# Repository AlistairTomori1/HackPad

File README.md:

# My HackPad

My HackPad is a 6-key (2x3) macropad built around the Seeed XIAO RP2040. It includes 2 EC11 rotary encoders (one for volume, one for timeline scrubbing) and a 0.91 inch 128x32 I2C OLED display (SSD1306) for status and layer info.

## Features
- 6x MX-style keys (2 columns x 3 rows matrix)
- 2x EC11 rotary encoder 1 for Volume, the other is for moving through video timeline
- 0.91 inch 128x32 I2C OLED (pin order: GND-VCC-SCL-SDA)
- KMK (CircuitPython) firmware with layers
- 3D-printed case designed to fit the PCB, OLED, and encoder cleanly

## Photos

## Schematic

Notes:
- Keys are wired as a 2x3 matrix with 1N4148 diodes to prevent ghosting.
- OLED uses I2C (SDA/SCL) and is powered from VBUS (5V).
- There are two encoders; each uses two GPIO pins plus a shared GND common (4 GPIO total).

## PCB

Notes:
- Switches are laid out on standard MX spacing.
- Diodes are placed close to their switches for clean routing.
- XIAO is positioned so the USB port is accessible at the board edge.
- Silkscreen includes the project name plus a "XIAO HERE" orientation label.

## Case and CAD

How it fits together:
- Top plate holds switches and keycaps.
- Middle cavity supports the PCB and provides clearance for solder joints.
- OLED sits above the key cluster.
- Encoder is mounted at the top-right with knob clearance.
- Bottom closes the case and provides mounting points.

(Designed for 3D printing.)

## Firmware Overview (KMK / CircuitPython)
This project uses KMK firmware (Python) for fast iteration.

Default behavior:
- Layer 0:
  - Keys: common editing macros (copy/paste/undo/redo, etc.)
  - Encoder 1: volume up/down
  - Encoder 2: timeline scrub (left/right)
- Layer 1:
  - Keys: media controls
  - Encoder 1: previous/next track
  - Encoder 2: fine scrub (Shift + left/right)

Firmware file:
- `firmware/main.py`

## BOM (Bill of Materials)
Everything needed to build this hackpad:

Electronics:
- 1x Seeed XIAO RP2040
- 6x MX-style switches
- 6x 1N4148 diodes (DO-35, through-hole)
- 2x EC11 rotary encoders
- 1x 0.91 inch 128x32 I2C OLED display (SSD1306, pin order: GND-VCC-SCL-SDA)
- 1x 1x4 2.54mm pin header (for the OLED)
- 1x PCB board

Hardware and Case:
- 6x Blank DSA keycaps (White)
- 3D-printed case (top and bottom, or top/middle/bottom depending on your design)
- 4x M3x16mm screws
- 4x M3 heatset inserts (5x4mm)

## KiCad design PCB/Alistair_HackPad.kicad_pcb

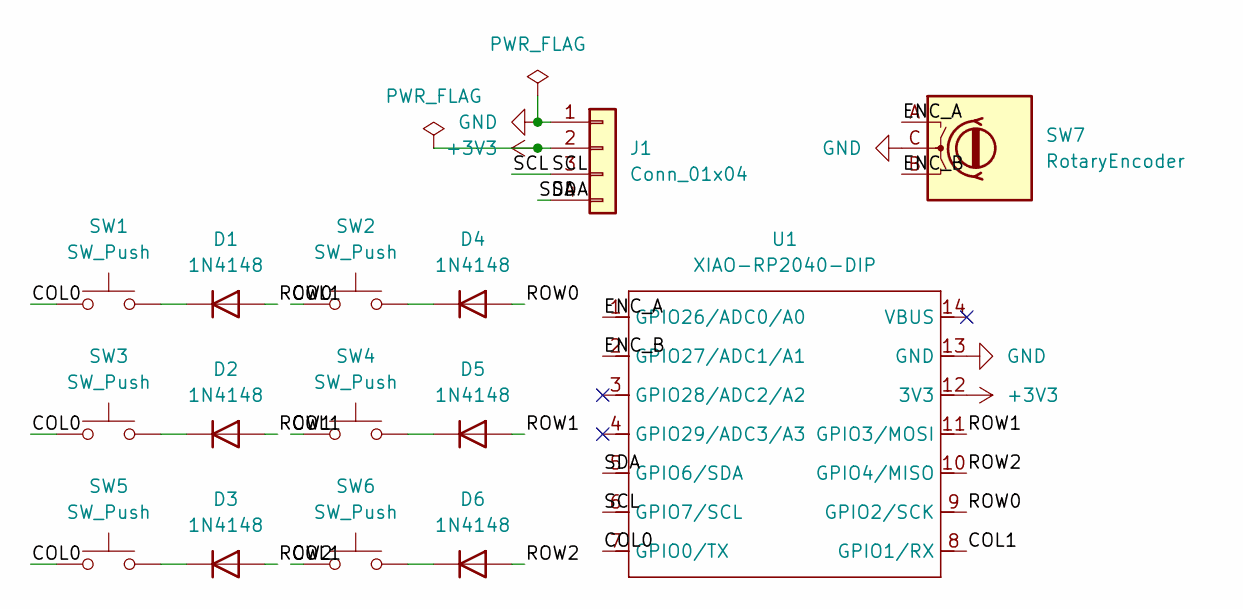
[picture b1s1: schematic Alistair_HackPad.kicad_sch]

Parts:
D1, D2, D3, D4, D5, D6: 1N4148; D_DO-35_SOD27_P7.62mm_Horizontal
J1: Conn_01x04; PinHeader_1x04_P2.54mm_Vertical
SW1, SW2, SW3, SW4, SW5, SW6: SW_Push; SW_Cherry_MX_1.00u_PCB
SW7: RotaryEncoder; RotaryEncoder_Alps_EC11E-Switch_Vertical_H20mm
U1: XIAO-RP2040-DIP

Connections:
+3V3: J1.2, U1.12 (3V3)
/COL0: SW1.1, SW3.1, SW5.1, U1.7 (GPIO0/TX)
/COL1: SW2.1, SW4.1, SW6.1, U1.8 (GPIO1/RX)
/ENC_A: SW7.A, U1.1 (GPIO26/ADC0/A0)
/ENC_B: SW7.B, U1.2 (GPIO27/ADC1/A1)
/ROW0: D1.2 (A), D4.2 (A), U1.9 (GPIO2/SCK)
/ROW1: D2.2 (A), D5.2 (A), U1.11 (GPIO3/MOSI)
/ROW2: D3.2 (A), D6.2 (A), U1.10 (GPIO4/MISO)
/SCL: J1.3, U1.6 (GPIO7/SCL)
/SDA: J1.4, U1.5 (GPIO6/SDA)
GND: J1.1, SW7.C, U1.13 (GND)
unnamed: D1.1 (K), SW1.2
unnamed: D2.1 (K), SW3.2
unnamed: D3.1 (K), SW5.2
unnamed: D4.1 (K), SW2.2
unnamed: D5.1 (K), SW4.2
unnamed: D6.1 (K), SW6.2

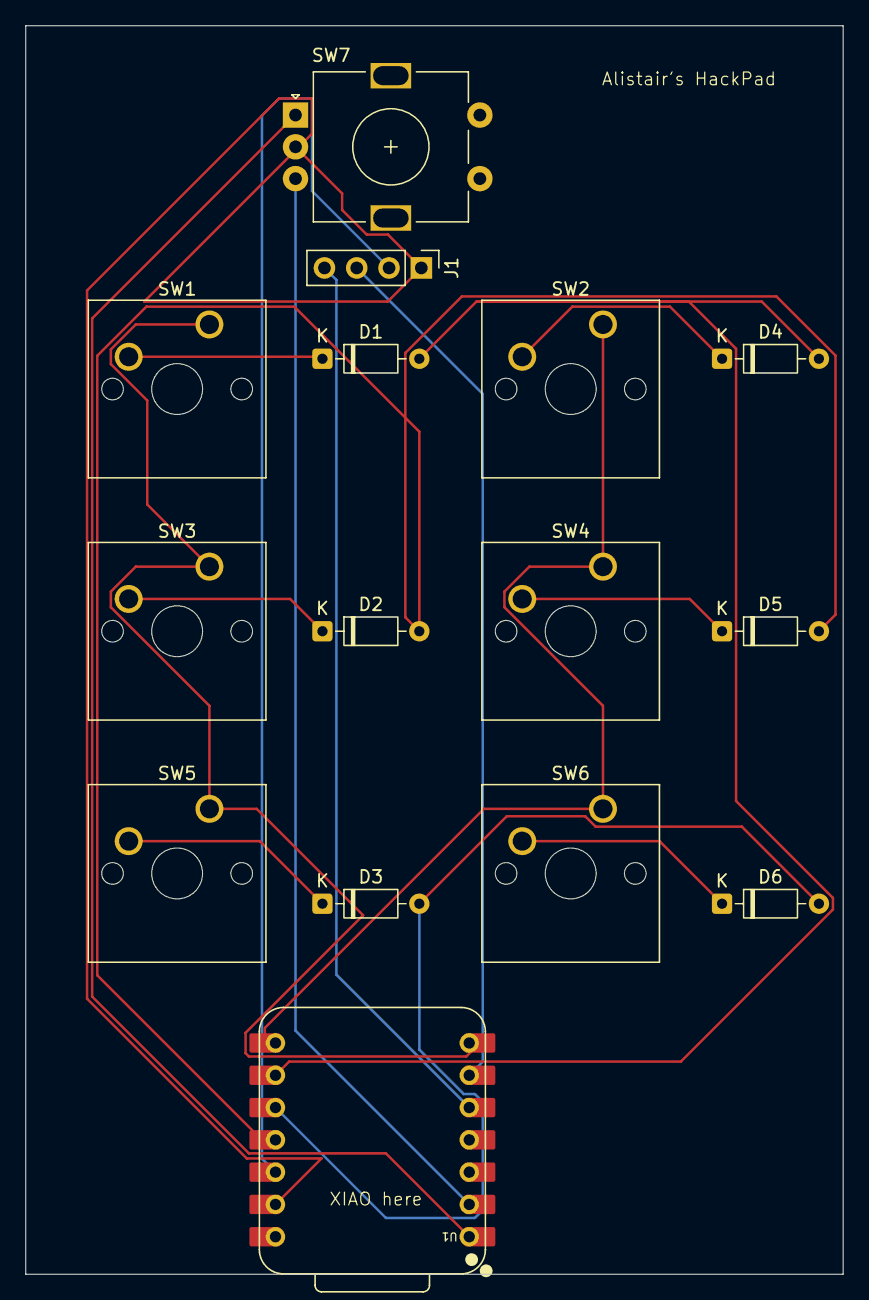
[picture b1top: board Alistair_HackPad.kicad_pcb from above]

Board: 2 copper layers, 64.3 x 98.2 mm, 15 parts (0 on the bottom side), 17 nets.

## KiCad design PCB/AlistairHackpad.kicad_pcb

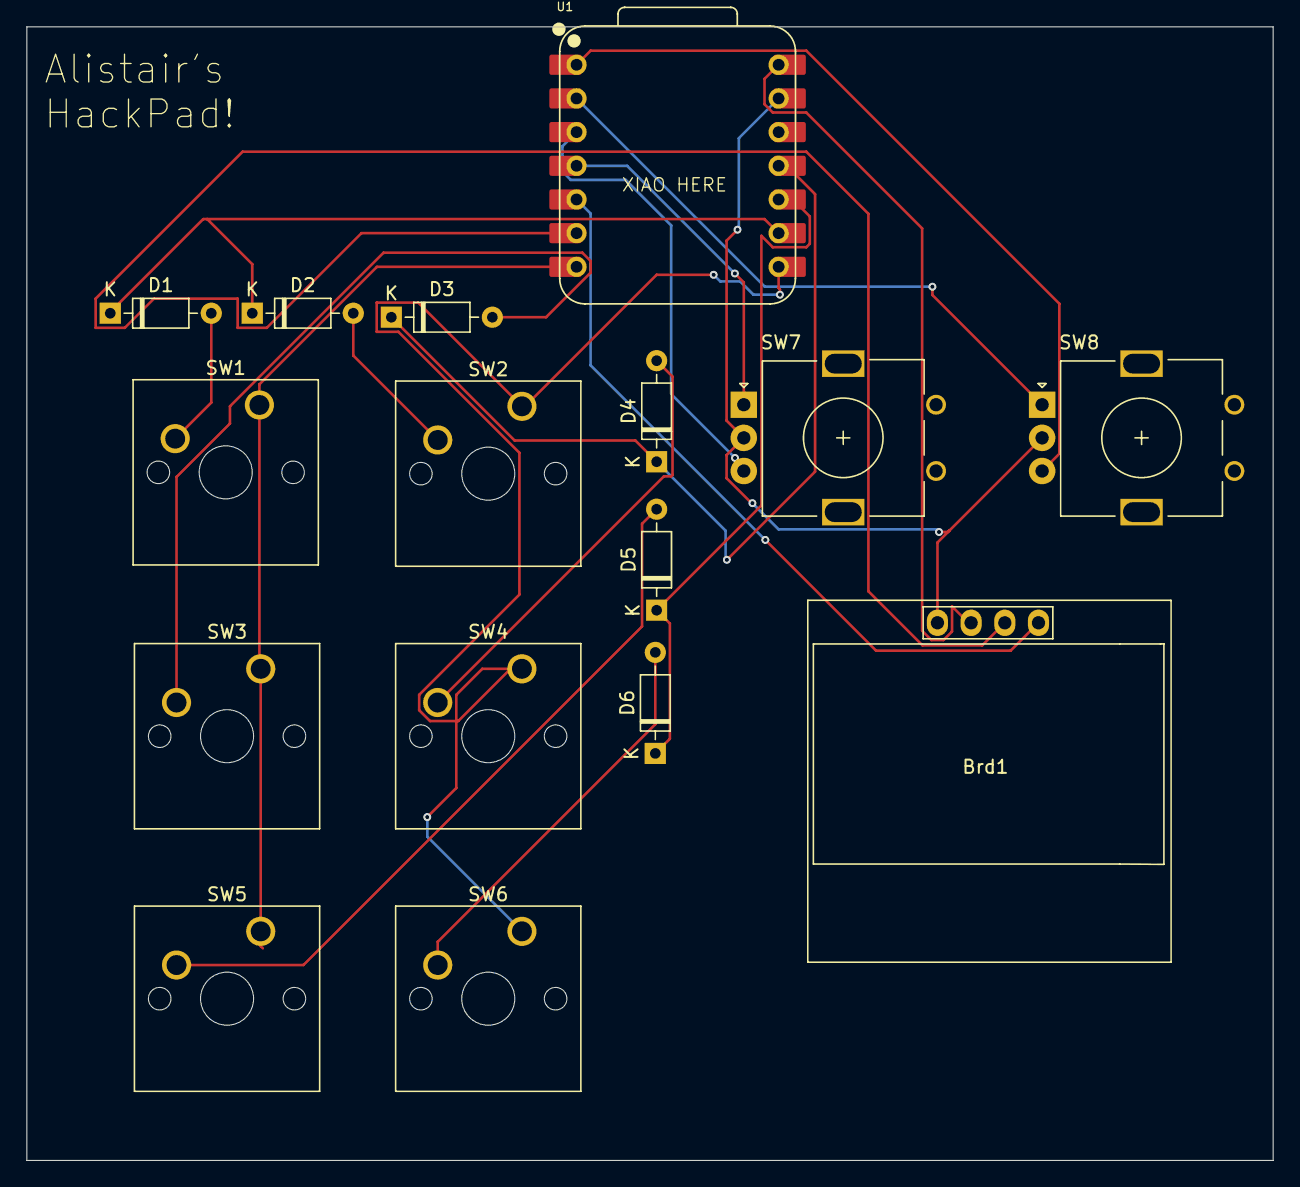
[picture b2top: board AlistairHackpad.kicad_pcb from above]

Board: 2 copper layers, 94.0 x 85.5 mm, 16 parts (0 on the bottom side), 19 nets.

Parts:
Brd1: SSD1306; 128x64OLED
D1, D2, D3, D4, D5, D6: D; D_DO-35_SOD27_P7.62mm_Horizontal
SW1, SW2, SW3, SW4, SW5, SW6: SW_Push; SW_Cherry_MX_1.00u_PCB
SW7, SW8: RotaryEncoder; RotaryEncoder_Alps_EC11E_Vertical_H20mm
U1: XIAO-RP2040-DIP

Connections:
+5V: Brd1.2 (VCC), U1.14 (VBUS)
GND: Brd1.1 (GND), SW7.C, SW8.C, U1.13 (GND)
unnamed: Brd1.3 (SCL), U1.6 (GPIO7/SCL)
unnamed: Brd1.4 (SDA), U1.5 (GPIO6/SDA)
unnamed: D1.2 (A), SW1.2
unnamed: D2.2 (A), SW2.2
unnamed: D3.2 (A), SW3.2
unnamed: D4.2 (A), SW4.2
unnamed: D5.2 (A), SW5.2
unnamed: D6.2 (A), SW6.2
unnamed: SW8.B, U1.1 (GPIO26/ADC0/A0)
unnamed: SW8.A, U1.2 (GPIO27/ADC1/A1)
unnamed: SW7.B, U1.3 (GPIO28/ADC2/A2)
unnamed: SW7.A, U1.4 (GPIO29/ADC3/A3)
col 1: SW1.1, SW3.1, SW5.1, U1.7 (GPIO0/TX)
col 2: SW2.1, SW4.1, SW6.1, U1.8 (GPIO1/RX)
row 1: D1.1 (K), D2.1 (K), U1.9 (GPIO2/SCK)
row 2: D3.1 (K), D4.1 (K), U1.11 (GPIO3/MOSI)
row 3: D5.1 (K), D6.1 (K), U1.10 (GPIO4/MISO)

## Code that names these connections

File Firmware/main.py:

import board

from kmk.kmk_keyboard import KMKKeyboard
from kmk.keys import KC
from kmk.scanners import DiodeOrientation
from kmk.modules.layers import Layers
from kmk.modules.encoder import EncoderHandler
from kmk.extensions.media_keys import MediaKeys

from kmk.extensions.oled import Oled, TextEntry


def pick(*names):
    for n in names:
        if hasattr(board, n):
            return getattr(board, n)
    raise ValueError("Missing pin names: " + ", ".join(names))


COL0 = pick("GP0", "D0")
COL1 = pick("GP1", "D1")

ROW0 = pick("GP2", "D2")
ROW1 = pick("GP3", "D3")
ROW2 = pick("GP4", "D4")

ENC_A = pick("GP26", "A0")
ENC_B = pick("GP27", "A1")

OLED_SDA = pick("GP6", "SDA", "D6")
OLED_SCL = pick("GP7", "SCL", "D7")


keyboard = KMKKeyboard()

keyboard.col_pins = (COL0, COL1)
keyboard.row_pins = (ROW0, ROW1, ROW2)

keyboard.diode_orientation = DiodeOrientation.COL2ROW

keyboard.extensions.append(MediaKeys())

layers = Layers()
keyboard.modules.append(layers)

encoder = EncoderHandler()
keyboard.modules.append(encoder)

encoder.pins = (
    (ENC_A, ENC_B, None, False, 4),
)

encoder.map = [
    ((KC.VOLD, KC.VOLU, KC.NO),),  
    ((KC.MPRV, KC.MNXT, KC.NO),),    
]

oled = Oled(
    sda=OLED_SDA,
    scl=OLED_SCL,
    width=128,
    height=32,
    entries=[
        TextEntry(text="Alistair HackPad", x=0, y=0),
        TextEntry(text="L0: EDIT", x=0, y=16, layer=0),
        TextEntry(text="L1: MEDIA", x=0, y=16, layer=1),
    ],
    dim_time=20,
    off_time=60,
)
keyboard.extensions.append(oled)

_______ = KC.TRNS

keyboard.keymap = [
    [
        KC.LGUI(KC.C),              KC.LGUI(KC.V),
        KC.LGUI(KC.Z),              KC.LGUI(KC.LSFT(KC.Z)),
        KC.LGUI(KC.SPC),            KC.MO(1),
    ],

    [
        KC.MPLY,                    KC.MUTE,
        KC.MPRV,                    KC.MNXT,
        KC.VOLD,                    _______,
    ],
]

if __name__ == "__main__":
    keyboard.go()

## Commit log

2025-12-29 Add README
2025-12-29 Adjusted HackPad Design
2025-12-29 Added seperate top and bottom files
2025-12-30 Added holes in top peice for the Rotary Encoders
